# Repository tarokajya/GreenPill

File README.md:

# GreenPill
Yet another Blue Pill

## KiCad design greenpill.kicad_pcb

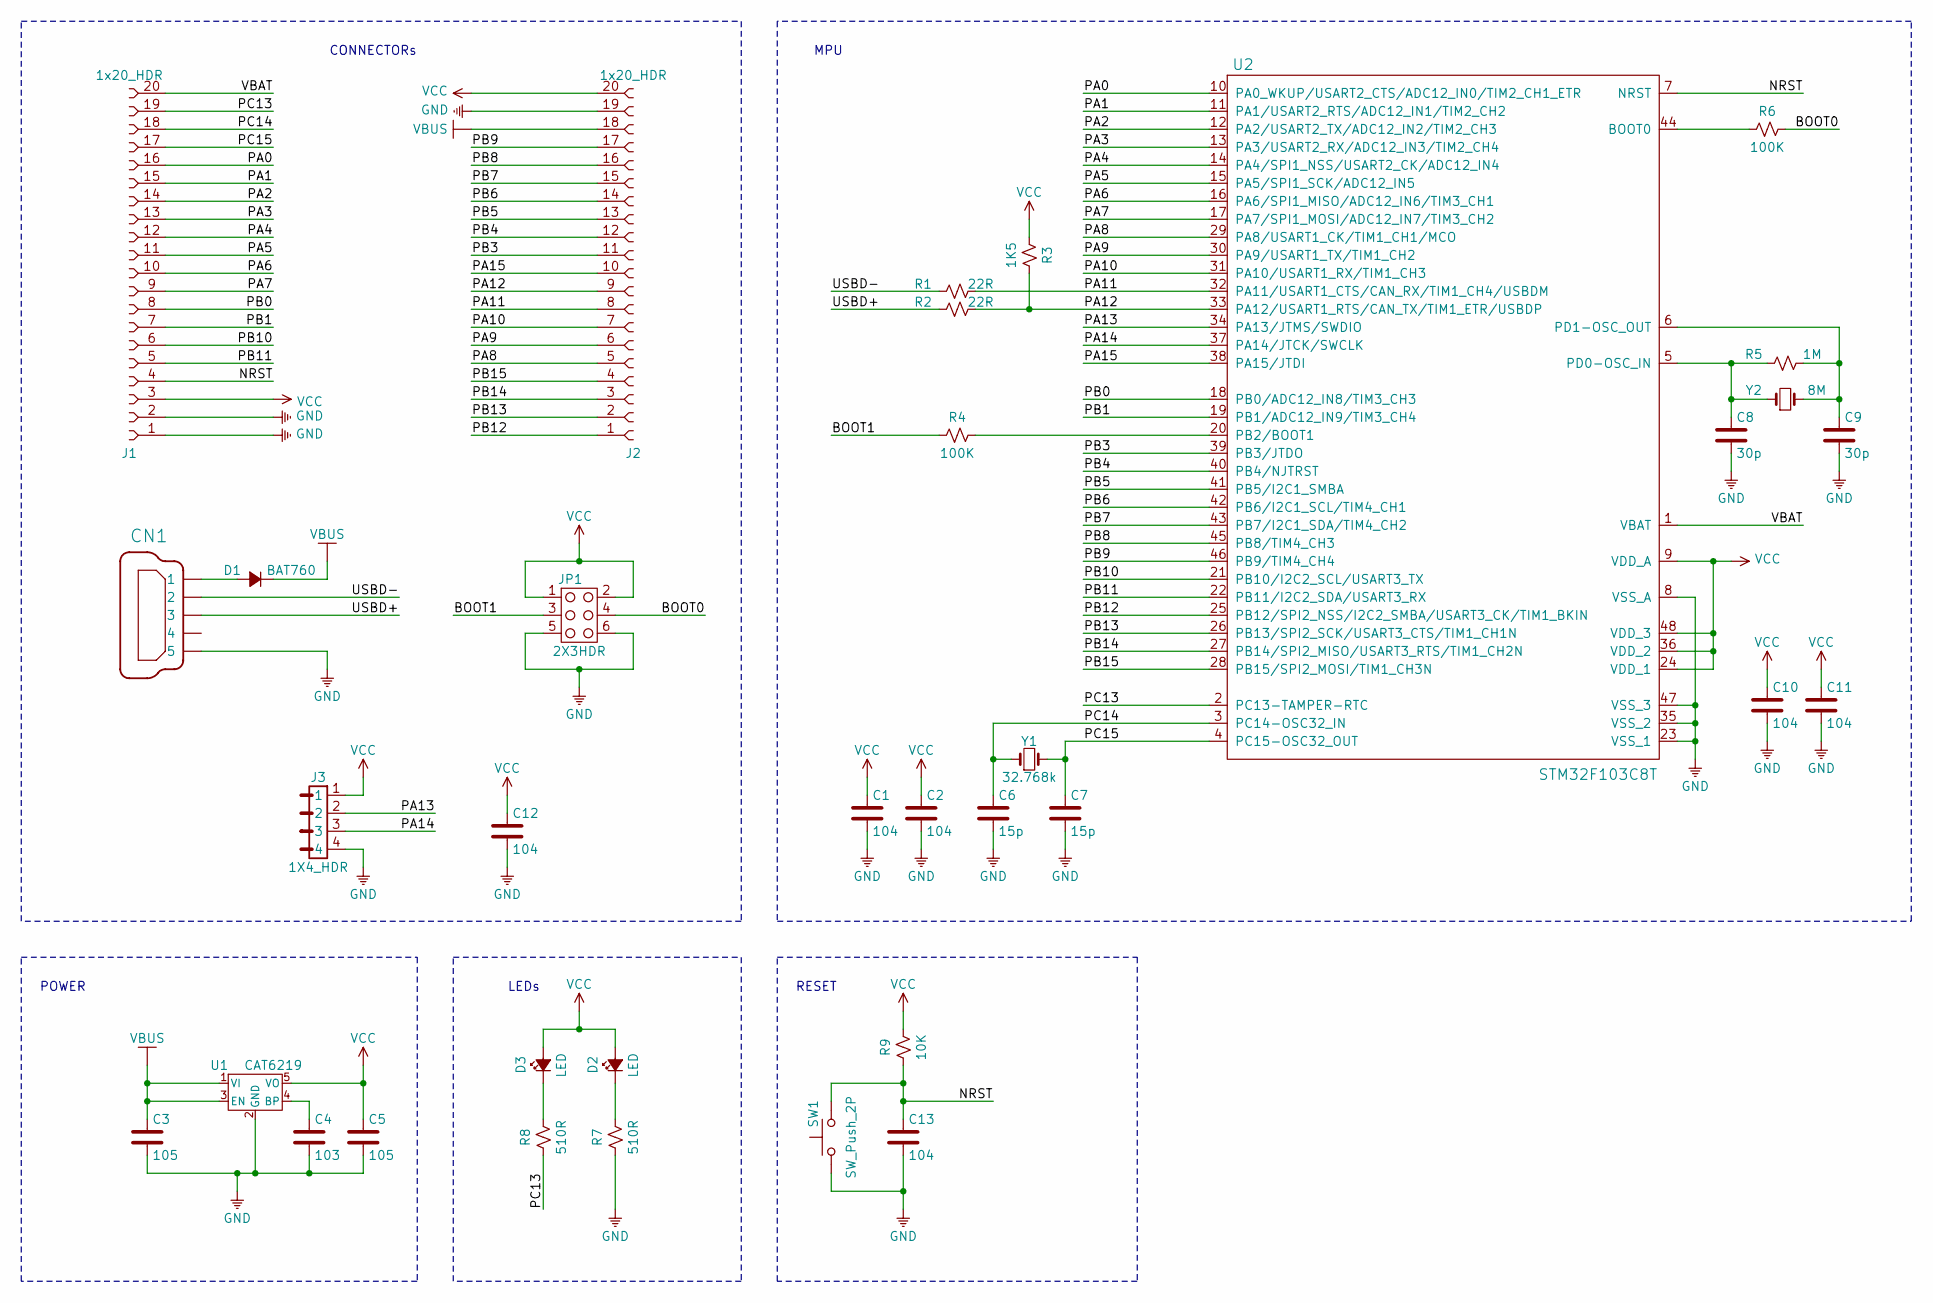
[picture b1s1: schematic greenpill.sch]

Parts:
C1, C2, C10, C11, C12, C13: 104; C0603
C3, C5: 105; C0603
C4: 103; C0603
C6, C7: 15p; C0603
C8, C9: 30p; C0603
CN1: CON-USB_5P; MUFY-051T-4BH806
D1: BAT760; SOD323
D2, D3: LED; LED_0603
J1, J2: 1x20_HDR; PinHeader_1X20_P2.54mm
J3: 1X4_HDR; PinHeader_1x4_P2.54mm
JP1: 2X3HDR; PinHeader_2x3_P2.54mm
R1, R2: 22R; R0603
R3: 1K5; R0603
R4, R6: 100K; R0603
R5: 1M; R0603
R7, R8: 510R; R0603
R9: 10K; R0603
SW1: SW_Push_2P; TSY3420
U1: CAT6219; SOT23-5
U2: STM32F103C8T; SOT313-2
Y1: 32.768k; X3215
Y2: 8M; Crystal_HC49-U_Vertical

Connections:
/BOOT0: JP1.4, R6.2
/BOOT1: JP1.3, R4.1
/NRST: C13.1, J1.4, R9.1, SW1.2, U2.7 (NRST)
/PA0: J1.16, U2.10 (PA0_WKUP/USART2_CTS/ADC12_IN0/TIM2_CH1_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)
/PA1: J1.15, U2.11 (PA1/USART2_RTS/ADC12_IN1/TIM2_CH2)
/PA2: J1.14, U2.12 (PA2/USART2_TX/ADC12_IN2/TIM2_CH3)
/PA3: J1.13, U2.13 (PA3/USART2_RX/ADC12_IN3/TIM2_CH4)
/PA4: J1.12, U2.14 (PA4/SPI1_NSS/USART2_CK/ADC12_IN4)
/PA5: J1.11, U2.15 (PA5/SPI1_SCK/ADC12_IN5)
/PA6: J1.10, U2.16 (PA6/SPI1_MISO/ADC12_IN6/TIM3_CH1)
/PA7: J1.9, U2.17 (PA7/SPI1_MOSI/ADC12_IN7/TIM3_CH2)
/PA8: J2.5, U2.29 (PA8/USART1_CK/TIM1_CH1/MCO)
/PA9: J2.6, U2.30 (PA9/USART1_TX/TIM1_CH2)
/PA10: J2.7, U2.31 (PA10/USART1_RX/TIM1_CH3)
/PA11: J2.8, R1.1, U2.32 (PA11/USART1_CTS/CAN_RX/TIM1_CH4/USBDM)
/PA12: J2.9, R2.1, R3.2, U2.33 (PA12/USART1_RTS/CAN_TX/TIM1_ETR/USBDP)
/PA13: J3.2, U2.34 (PA13/JTMS/SWDIO)
/PA14: J3.3, U2.37 (PA14/JTCK/SWCLK)
/PA15: J2.10, U2.38 (PA15/JTDI)
/PB0: J1.8, U2.18 (PB0/ADC12_IN8/TIM3_CH3)
/PB1: J1.7, U2.19 (PB1/ADC12_IN9/TIM3_CH4)
/PB3: J2.11, U2.39 (PB3/JTDO)
/PB4: J2.12, U2.40 (PB4/NJTRST)
/PB5: J2.13, U2.41 (PB5/I2C1_SMBA)
/PB6: J2.14, U2.42 (PB6/I2C1_SCL/TIM4_CH1)
/PB7: J2.15, U2.43 (PB7/I2C1_SDA/TIM4_CH2)
/PB8: J2.16, U2.45 (PB8/TIM4_CH3)
/PB9: J2.17, U2.46 (PB9/TIM4_CH4)
/PB10: J1.6, U2.21 (PB10/I2C2_SCL/USART3_TX)
/PB11: J1.5, U2.22 (PB11/I2C2_SDA/USART3_RX)
/PB12: J2.1, U2.25 (PB12/SPI2_NSS/I2C2_SMBA/USART3_CK/TIM1_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)
/PB13: J2.2, U2.26 (PB13/SPI2_SCK/USART3_CTS/TIM1_CH1N)
/PB14: J2.3, U2.27 (PB14/SPI2_MISO/USART3_RTS/TIM1_CH2N)
/PB15: J2.4, U2.28 (PB15/SPI2_MOSI/TIM1_CH3N)
/PC13: J1.19, R8.1, U2.2 (PC13-TAMPER-RTC)
/PC14: C6.1, J1.18, U2.3 (PC14-OSC32_IN), Y1.1
/PC15: C7.1, J1.17, U2.4 (PC15-OSC32_OUT), Y1.2
/USBD+: CN1.3, R2.2
/USBD-: CN1.2, R1.2
/VBAT: J1.20, U2.1 (VBAT)
GND: C1.2, C2.2, C3.2, C4.2, C5.2, C6.2, C7.2, C8.2, C9.2, C10.2, C11.2, C12.2, C13.2, CN1.5, J1.1, J1.2, J2.19, J3.4, JP1.5, JP1.6, R7.1, SW1.1, U1.2 (GND), U2.8 (VSS_A), U2.23 (VSS_1), U2.35 (VSS_2), U2.47 (VSS_3)
unnamed: C4.1, U1.4 (BP)
unnamed: C8.1, R5.1, U2.5 (PD0-OSC_IN), Y2.1
unnamed: C9.1, R5.2, U2.6 (PD1-OSC_OUT), Y2.2
unnamed: CN1.1, D1.2 (A)
unnamed: D2.1 (K), R7.2
unnamed: D3.1 (K), R8.2
unnamed: R4.2, U2.20 (PB2/BOOT1)
unnamed: R6.1, U2.44 (BOOT0)
VBUS: C3.1, D1.1 (K), J2.18, U1.1 (VI), U1.3 (EN)
VCC: C1.1, C2.1, C5.1, C10.1, C11.1, C12.1, D2.2 (A), D3.2 (A), J1.3, J2.20, J3.1, JP1.1, JP1.2, R3.1, R9.2, U1.5 (VO), U2.9 (VDD_A), U2.24 (VDD_1), U2.36 (VDD_2), U2.48 (VDD_3)

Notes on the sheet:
POWER
LEDs
RESET
CONNECTORs
MPU

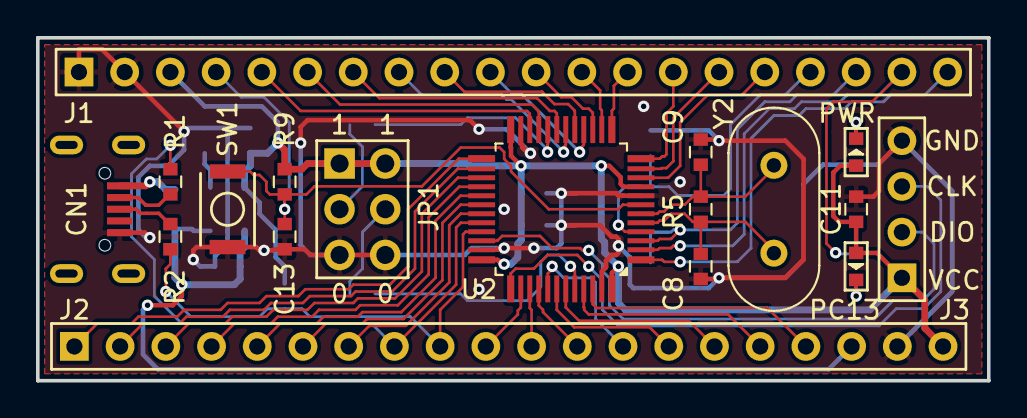
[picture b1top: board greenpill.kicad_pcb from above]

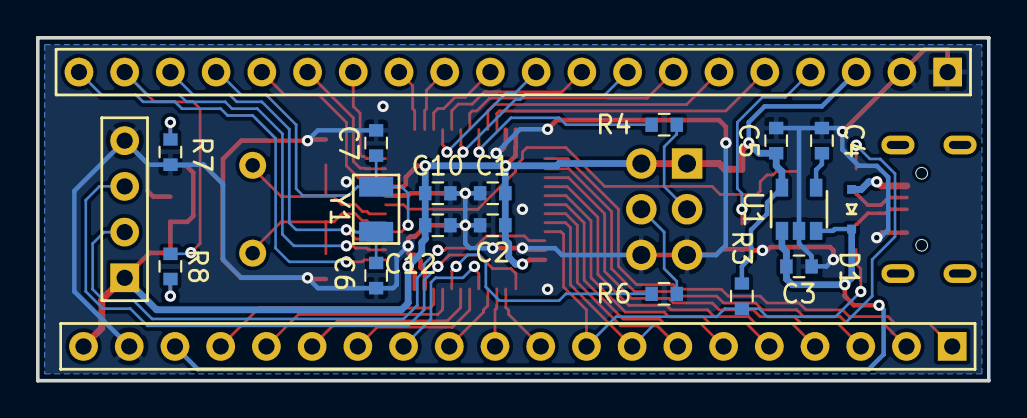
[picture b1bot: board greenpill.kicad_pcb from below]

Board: 2 copper layers, 52.8 x 19.0 mm, 35 parts (17 on the bottom side), 51 nets.

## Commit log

2019-11-06 add KiCad footprint.
2019-11-08 Update silk, routing.
2019-11-08 Update.
2019-11-08 Revert "Update."
    This reverts commit 947cbdeb3e8bb2312323af61bd7e8af29d60b43a.
2019-11-08 Update footprint table.
